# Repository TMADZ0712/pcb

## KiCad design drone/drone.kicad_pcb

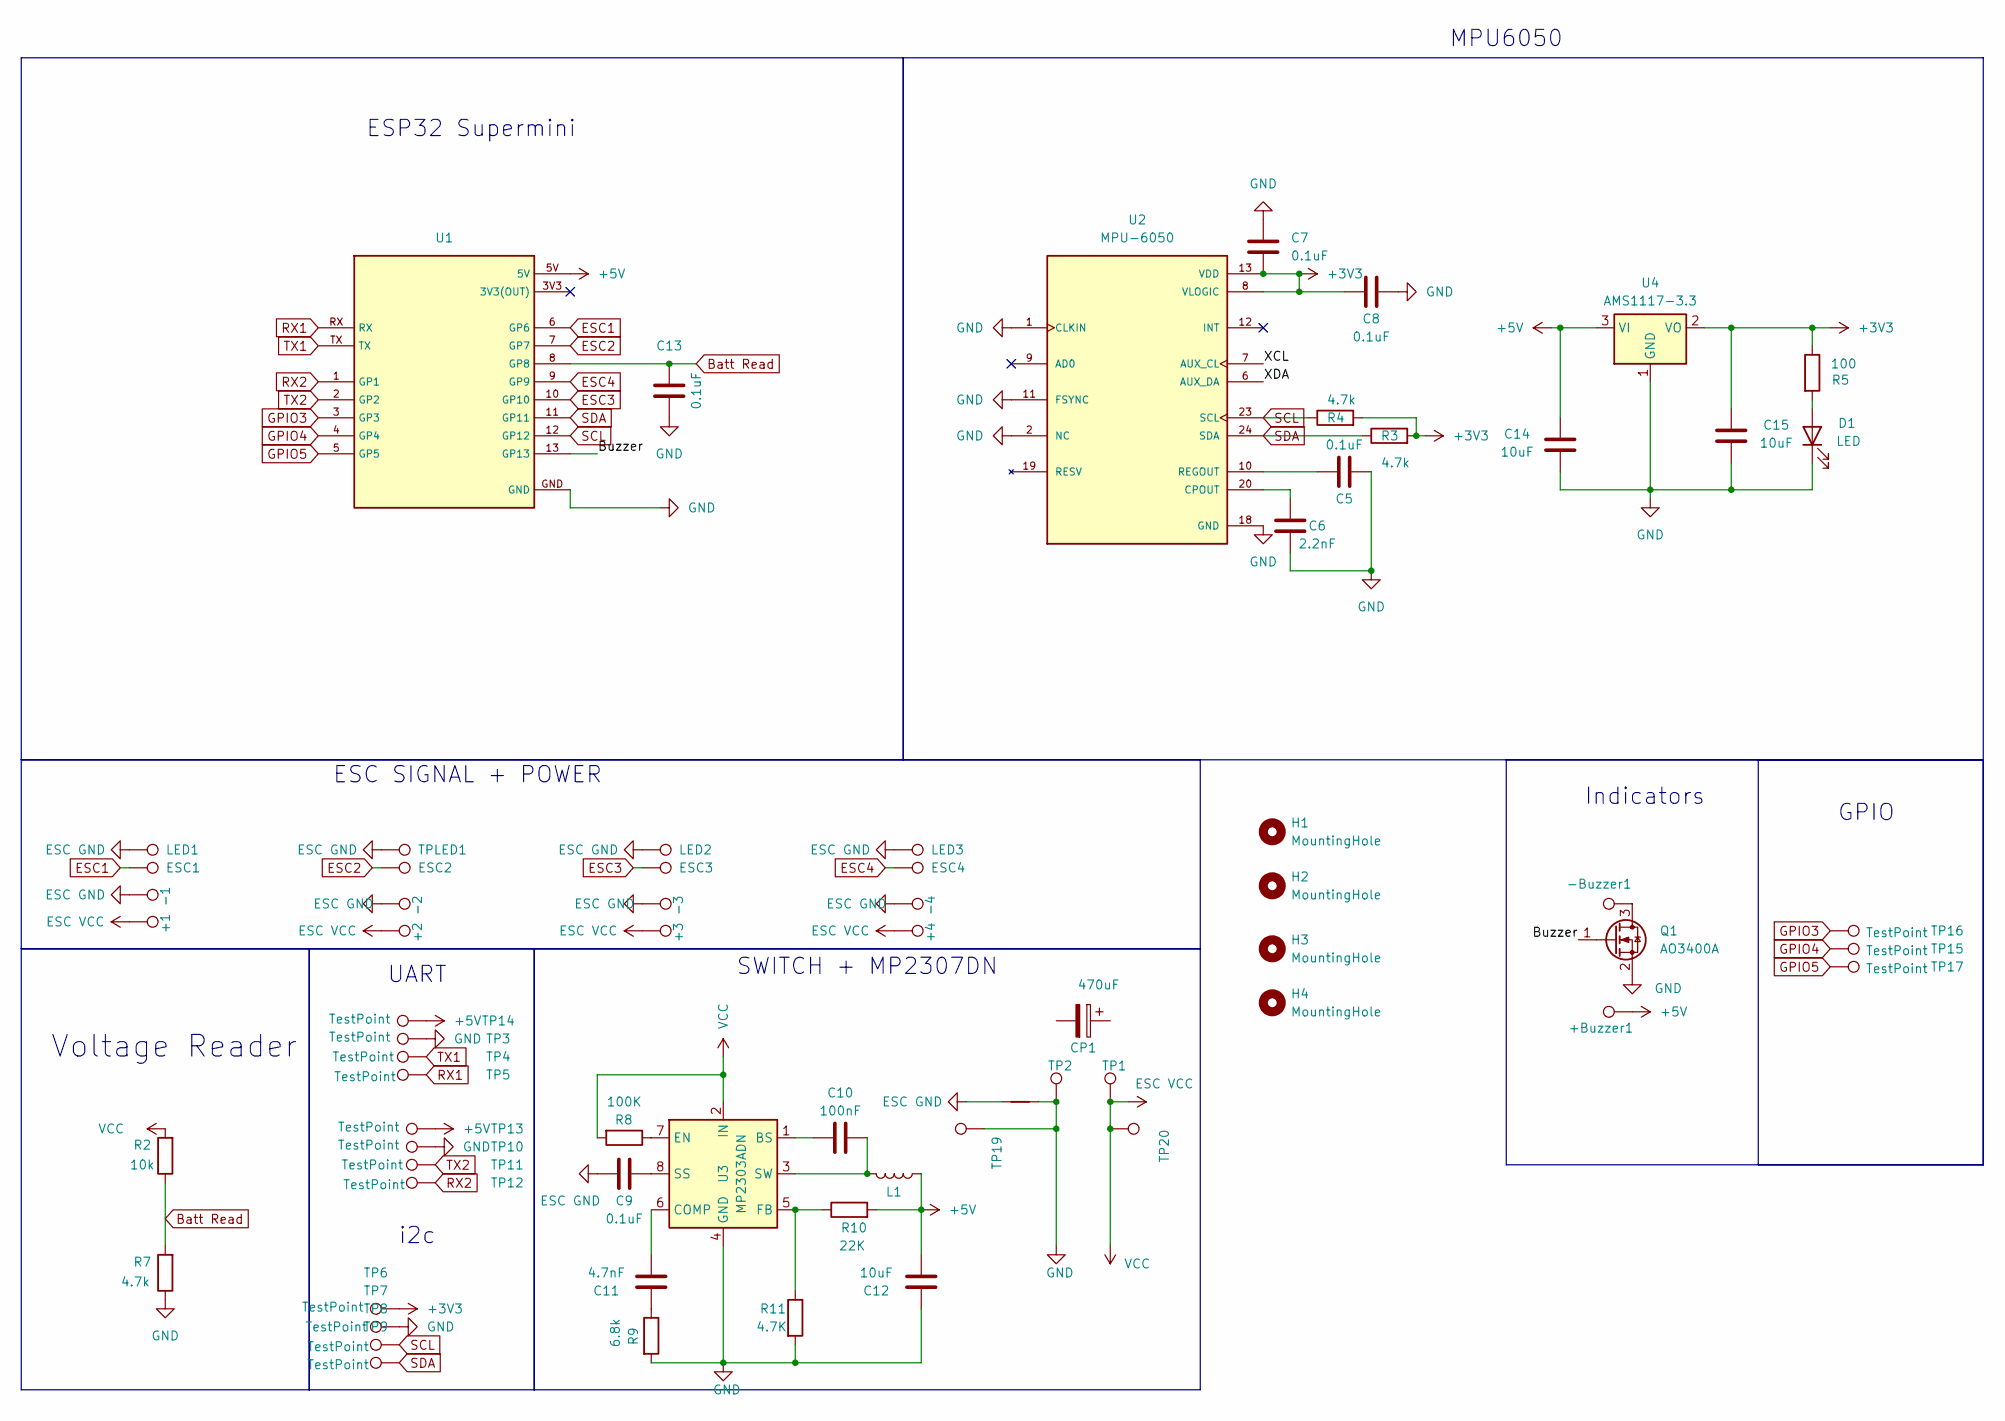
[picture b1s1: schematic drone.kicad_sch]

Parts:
+1, +2, +3, +4: TestPoint; TestPoint_Pad_1.5x1.5mm
+Buzzer1: TestPoint; TestPoint_Pad_1.0x1.0mm
-1, -2, -3, -4: TestPoint; TestPoint_Pad_1.5x1.5mm
-Buzzer1: TestPoint; TestPoint_Pad_1.0x1.0mm
C5, C7, C8, C9, C13: 0.1uF; C_0805_2012Metric_Pad1.18x1.45mm_HandSolder
C6: 2.2nF; C_0805_2012Metric_Pad1.18x1.45mm_HandSolder
C10: 100nF; C_0805_2012Metric_Pad1.18x1.45mm_HandSolder
C11: 4.7nF; C_0805_2012Metric_Pad1.18x1.45mm_HandSolder
C12, C14, C15: 10uF; C_0805_2012Metric_Pad1.18x1.45mm_HandSolder
CP1: 470uF
D1: LED; LED_0603_1608Metric
ESC1, ESC2, ESC3, ESC4: TestPoint; TestPoint_Pad_1.0x1.0mm
H1, H2, H3, H4: MountingHole; MountingHole_3.2mm_M3
L1: 10uH; L_Panasonic_PCC-M0630M
LED1, LED2, LED3: TestPoint; TestPoint_Pad_1.0x1.0mm
NT1: NetTie_2; NetTie-2_SMD_Pad2.0mm
Q1: AO3400A; SOT-23
R2: 10k; R_0805_2012Metric_Pad1.20x1.40mm_HandSolder
R3, R4, R7: 4.7k; R_0805_2012Metric_Pad1.20x1.40mm_HandSolder
R5: 100; R_0805_2012Metric_Pad1.20x1.40mm_HandSolder
R8: 100K; R_0805_2012Metric_Pad1.20x1.40mm_HandSolder
R9: 6.8k; R_0805_2012Metric_Pad1.20x1.40mm_HandSolder
R10: 22K; R_0805_2012Metric_Pad1.20x1.40mm_HandSolder
R11: 4.7K; R_0805_2012Metric_Pad1.20x1.40mm_HandSolder
TP1, TP2, TP19, TP20: TestPoint; TestPoint_Pad_2.5x2.5mm
TP3, TP4, TP5, TP6, TP7, TP8, TP9, TP10, TP11, TP12, TP13, TP14, TP15, TP16, TP17: TestPoint; TestPoint_Pad_D1.0mm
TPLED1: TestPoint; TestPoint_Pad_1.0x1.0mm
U1: ESP32-S3-SuperMini
U2: MPU-6050; QFN50P400X400X95-24N; PARTREV 3.4
U3: MP2303ADN; SOIC-8-1EP_3.9x4.9mm_P1.27mm_EP2.62x3.51mm
U4: AMS1117-3.3; SOT-223-3_TabPin2

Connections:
+3V3: C7.2, C8.2, C15.2, R3.2, R4.2, R5.1, TP6.1 (1_1), U2.8 (VLOGIC), U2.13 (VDD), U4.2 (VO)
+5V: +Buzzer1.1 (1_1), C12.1, C14.2, L1.1, R10.2, TP13.1 (1_1), TP14.1 (1_1), U1.5V, U4.3 (VI)
/<NO NET>: U2.7 (AUX_CL)
/Buzzer: Q1.1 (G), U1.13 (GP13)
/XDA: U2.6 (AUX_DA)
Batt Read: C13.1, R2.1, R7.2, U1.8 (GP8)
ESC1: ESC1.1 (1_1), U1.6 (GP6)
ESC2: ESC2.1 (1_1), U1.7 (GP7)
ESC3: ESC3.1 (1_1), U1.10 (GP10)
ESC4: ESC4.1 (1_1), U1.9 (GP9)
ESC GND: -1.1 (1_1), -2.1 (1_1), -3.1 (1_1), -4.1 (1_1), C9.2, LED1.1 (1_1), LED2.1 (1_1), LED3.1 (1_1), NT1.1, TPLED1.1 (1_1)
ESC VCC: +1.1 (1_1), +2.1 (1_1), +3.1 (1_1), +4.1 (1_1), R2.2, R8.2, TP1.1 (1_1), TP20.1 (1_1), U3.2 (IN)
GND: C5.2, C6.2, C7.1, C8.1, C12.2, C13.2, C14.1, C15.1, D1.1 (K), NT1.2, Q1.2 (S), R7.1, R9.2, R11.2, TP2.1 (1_1), TP3.1 (1_1), TP7.1 (1_1), TP10.1 (1_1), TP19.1 (1_1), U1.GND, U2.1 (CLKIN), U2.2 (NC), U2.3 (NC), U2.4 (NC), U2.5 (NC), U2.11 (FSYNC), U2.14 (NC), U2.15 (NC), U2.16 (NC), U2.17 (NC), U2.18 (GND), U3.4 (GND), U4.1 (GND)
GPIO3: TP16.1 (1_1), U1.3 (GP3)
GPIO4: TP15.1 (1_1), U1.4 (GP4)
GPIO5: TP17.1 (1_1), U1.5 (GP5)
unnamed: C11.2, R9.1
unnamed: D1.2 (A), R5.2
unnamed: -Buzzer1.1 (1_1), Q1.3 (D)
unnamed: C6.1, U2.20 (CPOUT)
unnamed: C5.1, U2.10 (REGOUT)
unnamed: C10.2, U3.1 (BS)
unnamed: C11.1, U3.6 (COMP)
unnamed: R8.1, U3.7 (EN)
unnamed: R10.1, R11.1, U3.5 (FB)
unnamed: C9.1, U3.8 (SS)
unnamed: C10.1, L1.2, U3.3 (SW)
RX1: TP5.1 (1_1), U1.RX
RX2: TP12.1 (1_1), U1.1 (GP1)
SCL: R4.1, TP8.1 (1_1), U1.12 (GP12), U2.23 (SCL)
SDA: R3.1, TP9.1 (1_1), U1.11 (GP11), U2.24 (SDA)
TX1: TP4.1 (1_1), U1.TX
TX2: TP11.1 (1_1), U1.2 (GP2)

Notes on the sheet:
Indicators
i2c
GPIO
SWITCH + MP2307DN
ESP32 Supermini
MPU6050
UART
Voltage Reader
ESC SIGNAL + POWER

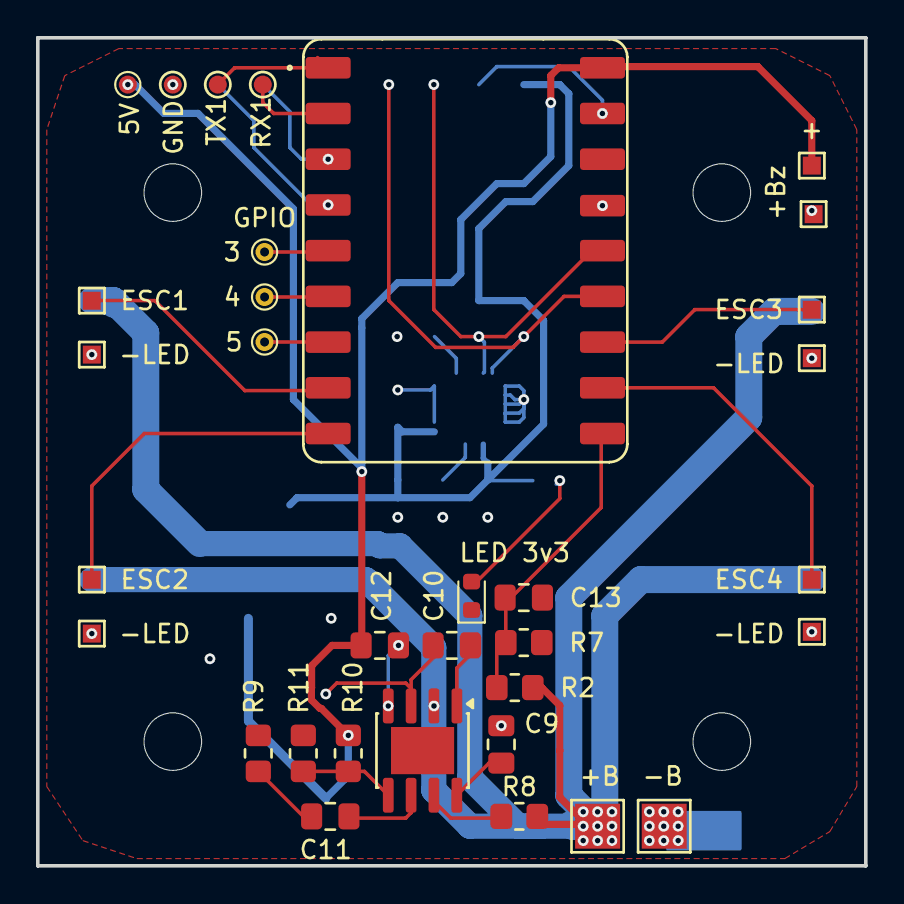
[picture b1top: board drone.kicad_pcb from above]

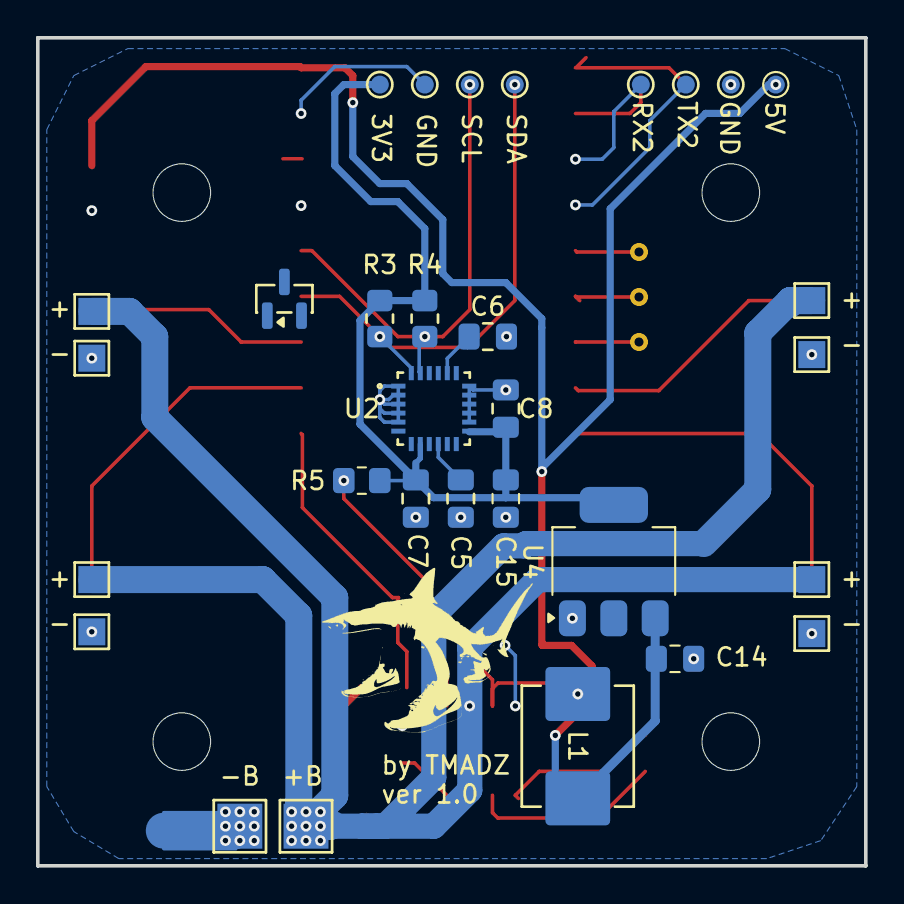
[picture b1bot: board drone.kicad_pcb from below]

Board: 2 copper layers, 46.0 x 46.0 mm, 69 parts (32 on the bottom side), 31 nets.

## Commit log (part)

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2026-04-14 14/4
2026-04-15 tiep tuc dj + gitignore
2026-04-15 esc wired
2026-04-16 copper pour 16/4
2026-04-16 drc + copper pour lai
2026-04-17 drc connect all
2026-04-17 DRC done, Gerber done
2026-04-18 tang width 3v3 len 0.4mm
2026-04-20 led with gnd
2026-04-20 wire led to gnd
2026-04-23 reduce size to 50mm, change testpoint pad
2026-04-24 size to 26.5, mp2307 to the back
2026-04-25 size 30.5 + esp32 s3 supermini
2026-04-26 drc 0
2026-04-27 add buzzer
2026-04-28 silk + external uart + i2c
2026-05-03 drc = 0, jlcpcb matched
2026-05-06 them 5v
2026-05-13 add ldo ams1117 3.3v
